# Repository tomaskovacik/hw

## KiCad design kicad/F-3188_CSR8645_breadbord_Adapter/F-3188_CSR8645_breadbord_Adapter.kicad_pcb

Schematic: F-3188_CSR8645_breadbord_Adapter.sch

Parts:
C1, C2: 100n; C_0805_HandSoldering
C3: 15p; C_0805_HandSoldering
D1, D2, D6: LED1; LED_1206_HandSoldering
D3, D4, D5: CG0603MLC-05E; R_0603_HandSoldering
D7: 1N4448; D_SOD-323_HandSoldering
J1: SCJ368R1NUS0B00G; 3.5mm_stereo_jack_PJ306M
J2: USB_B_Micro; USB_Micro-B
JP1: Jumper; SolderJumper-2_P1.3mm_Open_RoundedPad1.0x1.5mm
L1: 15nH; Choke_SMD_1206_Handsoldering
P1: CONN_01X22; Pin_Header_Straight_1x22
P2: CONN_01X21; Pin_Header_Straight_1x21
R1, R2, R5, R6: 10k; R_0805_HandSoldering
R3, R4, R9: 1k; R_0805_HandSoldering
R7, R8: 22; R_0805_HandSoldering
SW1: RESET; SW_SPST_FSMSM
SW2: VOL+; SW_SPST_FSMSM
SW3: VOL-; SW_SPST_FSMSM
SW4: NEXt; SW_SPST_FSMSM
SW5: PREV; SW_SPST_FSMSM
SW6: PLAY; SW_SPST_FSMSM
U1: F-3188_CSR8645; F-3188_CSR8645_no_silk_under_antena
U2: MIC; 3.5mm_stereo_jack_PJ320B

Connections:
5V: D5.1 (A1), D7.2 (A), J2.1 (VBUS)
/BAT: D7.1 (K), P1.14, R1.1, R2.1, R3.1, R4.1, R6.2, R9.1, U1.14 (BAT)
/HGND: J1.1, P2.3, U1.41 (SPK_L_N1)
/HL: J1.2, P2.4, U1.40 (SPK_R_P1)
/HR: J1.5, P2.2, U1.42 (SPK_L_P1)
/LED0: D2.1 (K), P1.3, U1.3 (LED0)
/LED1: D1.1 (K), P1.2, U1.2 (LED1)
/LED2: D6.1 (K), P1.1, U1.1 (LED2)
/MIC_AN: C1.1, P2.9, U1.35 (MIC_AN)
/MIC_AP: C2.2, P2.8, U1.36 (MIC_AP)
/MIC_BIAS: C1.2, P2.10, R5.1, U1.34 (MIC_BIAS)
/MIC_BN: P2.7, U1.37 (MIC_BN)
/MIC_BP: P2.6, U1.38 (MIC_BP)
/MUTE: P2.18, U1.26 (MUTE)
/NEXT: P2.13, SW4.2, U1.31 (NEXT)
/PLAY: P2.16, SW6.2, U1.28 (PLAY)
/POWER_ON: JP1.1, JP1.2, P1.15, R2.2, U1.15 (POWER_ON)
/PREV: P2.14, SW5.2, U1.30 (PREV)
/RST#: P1.13, R1.2, SW1.1, U1.13 (RST#)
/USB+: P2.19, R7.1, U1.25 (USB_P)
/USB-: P2.20, R8.1, U1.24 (USB_N)
/VOLDOWN: P2.12, SW3.2, U1.32 (VOLDOWN)
/VOLUP: P2.11, SW2.2, U1.33 (VOLUP)
GND: C3.2, D3.2 (A2), D4.2 (A2), D5.2 (A2), J2.5 (GND), J2.6 (Shield), P1.17, SW1.2, U1.17 (GND), U2.1
unnamed: C2.1, C3.1, L1.1, R5.2
unnamed: D1.2 (A), R9.2
unnamed: D2.2 (A), R4.2
unnamed: D3.1 (A1), J2.3 (D+), R7.2
unnamed: D4.1 (A1), J2.2 (D-), R8.2
unnamed: D6.2 (A), R3.2
unnamed: L1.2, U2.2
unnamed: P1.4, U1.4 (AIO0)
unnamed: P1.5, U1.5 (MISO)
unnamed: P1.6, U1.6 (CSB)
unnamed: P1.7, U1.7 (SPI_CLK)
unnamed: P1.8, U1.8 (MOSI)
unnamed: P1.9, U1.9 (SPI_PCM)
unnamed: P1.10, U1.10 (TX)
unnamed: P1.11, U1.11 (RX)
unnamed: P1.12, U1.12 (VBUS)
unnamed: P1.16, U1.16 (1V8)
unnamed: P1.18, U1.18 (CHG_EXT)
unnamed: P1.19, U1.19 (BAT_SENSE)
unnamed: P1.20, U1.20 (PIO10)
unnamed: P1.21, U1.21 (PIO11)
unnamed: P1.22, U1.22 (PIO12)
unnamed: P2.1, U1.43 (AGND)
unnamed: P2.5, U1.39 (SPK_R_N1)
unnamed: P2.15, U1.29 (GPIO8)
unnamed: P2.17, U1.27 (GPIO6)
unnamed: P2.21, U1.23 (PIO13)
unnamed: R6.1, SW2.1, SW3.1, SW4.1, SW5.1, SW6.1

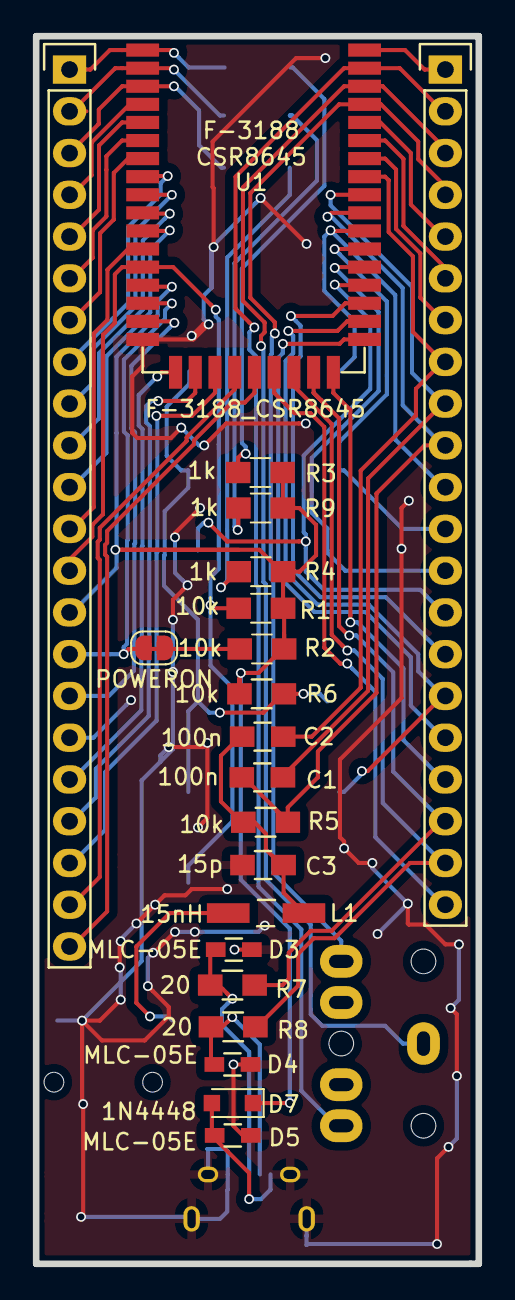
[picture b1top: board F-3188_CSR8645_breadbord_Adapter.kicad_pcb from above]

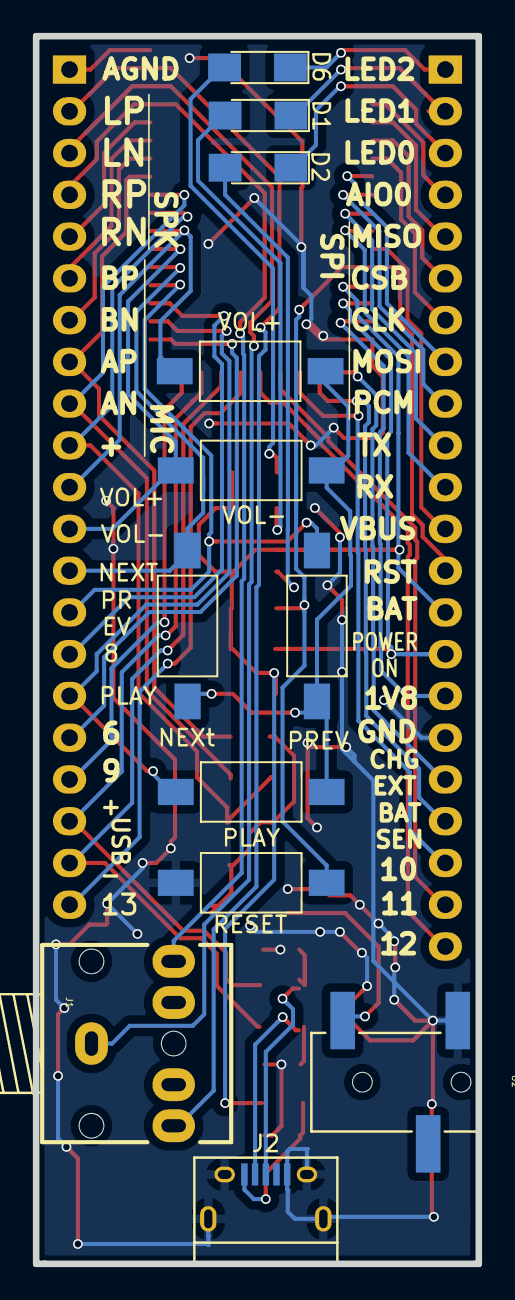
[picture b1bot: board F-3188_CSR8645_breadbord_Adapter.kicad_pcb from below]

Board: 2 copper layers, 26.9 x 74.7 mm, 33 parts (12 on the bottom side), 52 nets.

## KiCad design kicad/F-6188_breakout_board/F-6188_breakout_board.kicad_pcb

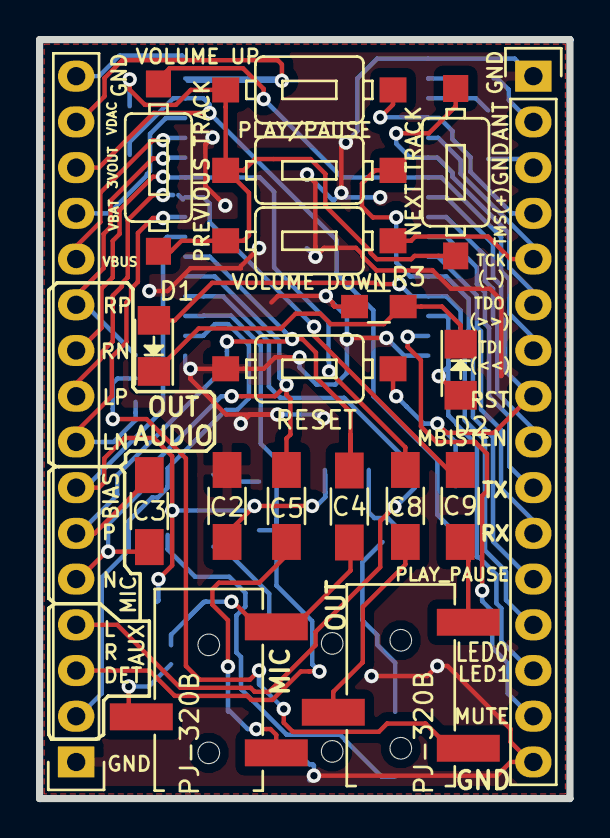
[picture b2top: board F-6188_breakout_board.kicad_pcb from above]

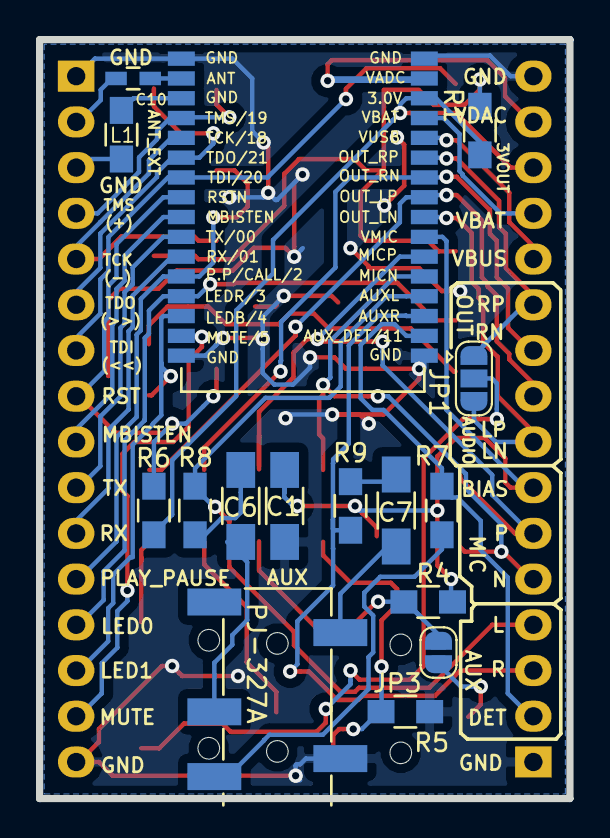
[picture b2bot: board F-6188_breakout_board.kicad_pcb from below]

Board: 2 copper layers, 29.5 x 42.2 mm, 35 parts (16 on the bottom side), 44 nets.

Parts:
C1: 100n/50V X7R!!!; C_1206_HandSoldering
C2: 1u/16V; C_1206_HandSoldering
C3: 10n/50V X7R!!!; C_1206_HandSoldering
C4, C5: 1u/16V X7R; C_1206_HandSoldering
C6, C7: 1u/25V; C_1206_HandSoldering
C8, C9: CKS1206 10u/25V X5R 10% SAMSUNG; C_1206_HandSoldering
C10: 2.2p; C_0603_HandSoldering
CON1, CON2: CONN_16; Pin_Header_Straight_1x16
D1, D2: LED; LED-1206
JP1: Jumper_3_Bridged12; SolderJumper-3_P1.3mm_Open_RoundedPad1.0x1.5mm
JP3: Jumper_NO_Small; SolderJumper-2_P1.3mm_Open_RoundedPad1.0x1.5mm
L1: 100nH*; R_0805_HandSoldering
R1, R6: 10k; R_0805_HandSoldering
R3, R4, R5, R7, R8, R9: 1k; R_0805_HandSoldering
SW1: VOLUME UP; 3x6x2.5mm_tact_switch
SW2: VOLUME DOWN; 3x6x2.5mm_tact_switch
SW3: NEXT TRACK; 3x6x2.5mm_tact_switch
SW4: PREVIOUS TRACK; 3x6x2.5mm_tact_switch
SW5: PLAY/PAUSE; 3x6x2.5mm_tact_switch
SW6: RESET; 3x6x2.5mm_tact_switch
U1: F-6188
U2, U3: PJ-320B; 3.5mm_stereo_jack_PJ320B
U4: PJ-327A

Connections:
/3V_OUT: CON1.14, R1.1, R6.1, U1.30
/#RST: CON2.8, R6.2, SW6.2, U1.8
/ANT_EXT: C10.1, U1.2
/AUDIO_LN: CON1.8, JP1.3, U1.24
/AUDIO_LP: C9.1, CON1.9, U1.25
/AUDIO_RN: CON1.11, JP1.1, U1.27
/AUDIO_RP: C8.1, CON1.10, U1.26
/AUX_DETECT: CON1.2, R7.1, U1.18
/AUX_INL: CON1.4, R8.1, U1.20
/AUX_INR: CON1.3, R9.1, U1.19
/LED0: CON2.13, D1.2, U1.13
/LED1: CON2.14, D2.2, U1.14
/MBISTEN: CON2.9, U1.9
/MICN: C3.1, C5.1, CON1.5, U1.21
/MICP: C3.2, C4.1, CON1.6, U1.22
/MIC_BIAS: C1.2, C2.1, CON1.7, R4.2, U1.23
/MUTE: CON2.15, U1.15
/PLAY_PAUSE: CON2.12, SW5.2, U1.12
/RX: CON2.11, U1.11
/TCK: CON2.5, SW2.2, U1.5
/TDI: CON2.7, SW4.2, U1.7
/TDO: CON2.6, SW3.2, U1.6
/TMS: CON2.4, SW1.2, U1.4
/TX: CON2.10, U1.10
/VBAT: CON1.13, U1.29
/VBUS: CON1.12, U1.28
/VDAC: CON1.15, U1.31
GND: C1.1, C2.2, CON1.1, CON1.16, CON2.1, CON2.16, R3.2, R5.1, SW6.1, U1.1, U1.16, U1.17, U1.32, U4.3
unnamed: C4.2, JP3.1, R4.1, U2.2
unnamed: C5.2, R5.2, U2.1
unnamed: C6.1, R8.2
unnamed: C6.2, U4.5
unnamed: C7.1, R9.2
unnamed: C7.2, U4.2
unnamed: C8.2, U3.3
unnamed: C9.2, U3.2
unnamed: C10.2, CON2.2
unnamed: CON2.3, L1.2
unnamed: D1.1, D2.1, R3.1
unnamed: JP1.2, U3.1
unnamed: JP3.2, U2.3
unnamed: L1.1, U1.3
unnamed: R1.2, SW1.1, SW2.1, SW3.1, SW4.1, SW5.1
unnamed: R7.2, U4.4

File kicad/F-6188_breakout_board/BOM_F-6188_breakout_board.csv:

"Id";"Designator";"Package";"Quantity";"Designation";"Supplier and ref";
1;"SW6";"3x6x2.5mm_tact_switch";1;"RESET";;;
2;"SW3";"3x6x2.5mm_tact_switch";1;"NEXT TRACK";;;
3;"SW4";"3x6x2.5mm_tact_switch";1;"PREVIOUS TRACK";;;
4;"SW2";"3x6x2.5mm_tact_switch";1;"VOLUME DOWN";;;
5;"SW5";"3x6x2.5mm_tact_switch";1;"PLAY/PAUSE";;;
6;"SW1";"3x6x2.5mm_tact_switch";1;"VOLUME UP";;;
7;"U2,U3";"3.5mm_stereo_jack_PJ320B";2;"PJ-320B";;;
8;"C2";"TantalC_SizeA_EIA-3216_HandSoldering";1;"CTS 1u/16V A 10% AVX-TAJ";;;
9;"CON1,CON2";"Pin_Header_Straight_1x16";2;"CONN_16";;;
10;"D1,D2";"LED-1206";2;"LED";;;
11;"R1,R6";"R_0805_HandSoldering";2;"10k";;;
12;"R2,R3,R7,R8,R9";"R_0805_HandSoldering";5;"1k";;;
13;"R4,R5";"R_0805_HandSoldering";2;"1k2";;;
14;"U1";"F-6188";1;"F-6188";;;
15;"U4";"PJ-327A";1;"PJ-327A";;;
16;"C1,C3";"C_1206_HandSoldering";2;"100n/50V X7R!!!";;;
17;"C6,C7,C8,C9";"C_1206_HandSoldering";4;"CKS1206 10u/25V X5R 10% SAMSUNG";;;
18;"JP2";"SolderJumper-2_P1.3mm_Open_RoundedPad1.0x1.5mm";1;"Jumper_2";;;
19;"JP1";"SolderJumper-3_P1.3mm_Open_RoundedPad1.0x1.5mm";1;"Jumper_3_Bridged12";;;
20;"JP3";"SolderJumper-2_P1.3mm_Open_RoundedPad1.0x1.5mm";1;"Jumper_NO_Small";;;
21;"C4,C5";"C_1206_HandSoldering";2;"1u/16V X7R";;;

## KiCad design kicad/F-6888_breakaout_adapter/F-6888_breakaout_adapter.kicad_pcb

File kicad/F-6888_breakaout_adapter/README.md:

# IMPORTANT NOTE

take care what module you buy, where are version which did not have support for all features,read description of what you buy, for example here from aliexpress:

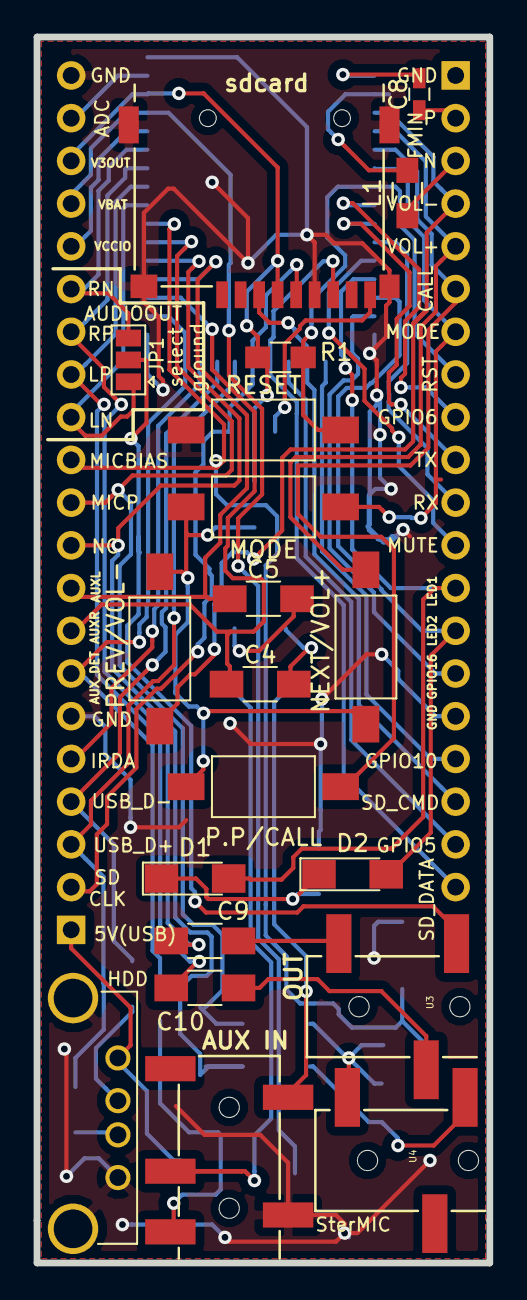
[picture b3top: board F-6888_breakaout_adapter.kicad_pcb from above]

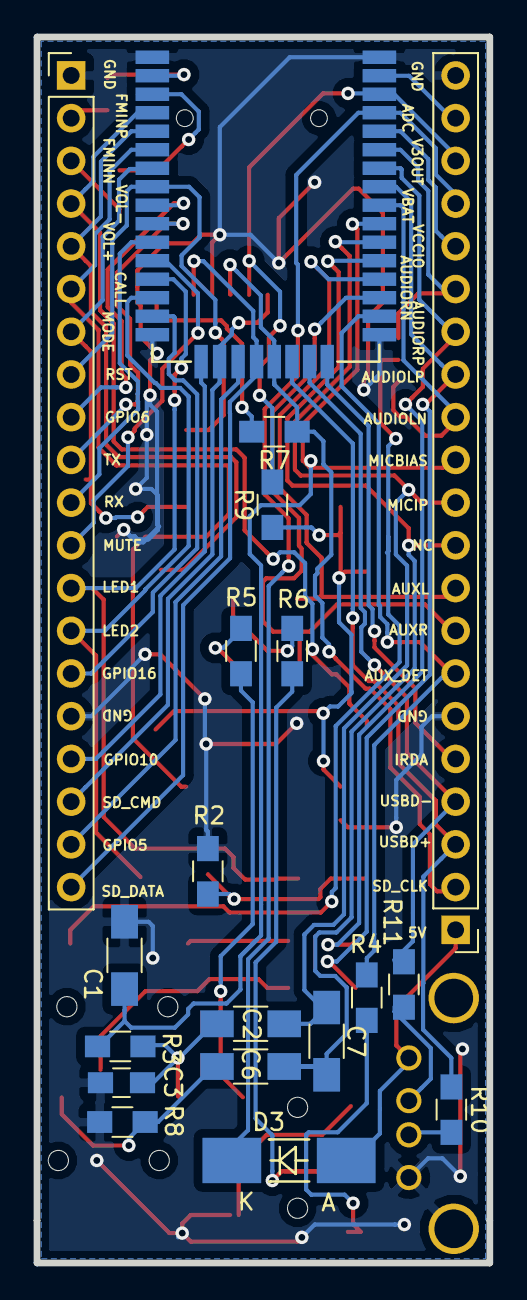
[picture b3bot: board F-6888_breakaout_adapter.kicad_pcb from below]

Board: 2 copper layers, 26.9 x 72.9 mm, 39 parts (19 on the bottom side), 55 nets.

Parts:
C1, C2, C4, C5, C9, C10: 1uF; C_1206_HandSoldering
C3: 100p; C_0805_HandSoldering
C6: 1uF*; C_1206_HandSoldering
C7: 10n(*); C_1206_HandSoldering
C8: 2.2p; C_0603_HandSoldering
D1, D2: LED; LED_1206_HandSoldering
D3: D; MELF_Handsoldering
J1: USB_A
J2: CONN_01X20; Pin_Header_Straight_1x20_Pitch2.54mm
J4: CONN_01X20; Pin_Header_Straight_1x21_Pitch2.54mm
J6: Micro_SD_Card_Det; Conn_uSDcard
JP1: Jumper_NC_Dual; SolderJumper-3_P1.3mm_Open_Pad1.0x1.5mm
L1: 100nH*; R_0805_HandSoldering
R1, R9: 10k; R_0805_HandSoldering
R2, R3, R4, R5, R6: 1k; R_0805_HandSoldering
R7: 3k3; R_0805_HandSoldering
R8: 1k*; R_0805_HandSoldering
R10, R11: 200; R_0805_HandSoldering
SW1: RESET; SW_SPST_FSMSM
SW2: PREV/VOL-; SW_SPST_FSMSM
SW3: NEXT/VOL+; SW_SPST_FSMSM
SW4: P.P/CALL; SW_SPST_FSMSM
SW5: MODE; SW_SPST_FSMSM
U1: F-6888
U2: PJ-327A
U3, U4: PJ-320B; 3.5mm_stereo_jack_PJ320B

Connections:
/5V: D3.2, J1.1, J4.1
/ADC: J4.20, U1.39
/AUDIOLN: J4.13, JP1.1, U1.32
/AUDIOLP: C10.2, J4.14, U1.33
/AUDIORN: J4.16, JP1.3, U1.35
/AUDIORP: C9.2, J4.15, U1.34
/AUXL: C5.1, J4.9, U1.28
/AUXR: C4.1, J4.8, U1.27
/AUX_DET: J4.7, R4.1, U1.26
/FMINN: L1.2, U1.3
/FMINP: C8.2, U1.2
/GPIO5: J2.19, U1.19
/GPIO6: J2.9, U1.9
/GPIO10: J2.17, U1.17
/GPIO16: J2.15, U1.15
/IRDA: J4.5, U1.24
/LED1: D1.2, J2.13, U1.13
/LED2: D2.2, J2.14, U1.14
/MICBIAS: C1.1, J4.12, R3.2, U1.31
/MICIP: C2.2, C7.1, J4.11, U1.30
/MODE: J2.7, SW5.2, U1.7
/MUTE: J2.12, U1.12
/NC: C6.1, C7.2, J4.10, U1.29
/NEXT/VOL+: J2.5, SW3.2, U1.5
/P.P/CALL: J2.6, SW4.2, U1.6
/PREV/VOL-: J2.4, SW2.2, U1.4
/RSTN: J2.8, R1.1, SW1.2, U1.8
/RX: J2.11, U1.11
/SD_CLK: J4.2, J6.5, R7.1, U1.21
/SD_CMD: J2.18, J6.3, U1.18
/SD_DATA: J2.20, J6.7, U1.20
/TX: J2.10, U1.10
/USBD+: J4.3, R10.1, U1.22
/USBD-: J4.4, R11.2, U1.23
/V3OUT: J4.19, J6.4, R1.2, R9.2, U1.38
/VBAT: D3.1, J4.18, U1.37
/VCCIO: J4.17, U1.36
GND: C1.2, C3.2, J1.4, J1.5, J2.1, J2.16, J4.6, J4.21, J6.6, R2.2, R8.1, SW1.1, U1.1, U1.16, U1.25, U1.40, U2.3
unnamed: C2.1, C3.1, R3.1, U4.2
unnamed: C4.2, R5.1
unnamed: C5.2, R6.1
unnamed: C6.2, R8.2, U4.1
unnamed: C8.1, J2.2
unnamed: C9.1, U3.2
unnamed: C10.1, U3.3
unnamed: D1.1, D2.1, R2.1
unnamed: J1.2, R11.1
unnamed: J1.3, R10.2
unnamed: J2.3, L1.1
unnamed: J6.9, R7.2
unnamed: JP1.2, U3.1
unnamed: R4.2, U2.4
unnamed: R5.2, U2.2
unnamed: R6.2, U2.5
unnamed: R9.1, SW2.1, SW3.1, SW4.1, SW5.1

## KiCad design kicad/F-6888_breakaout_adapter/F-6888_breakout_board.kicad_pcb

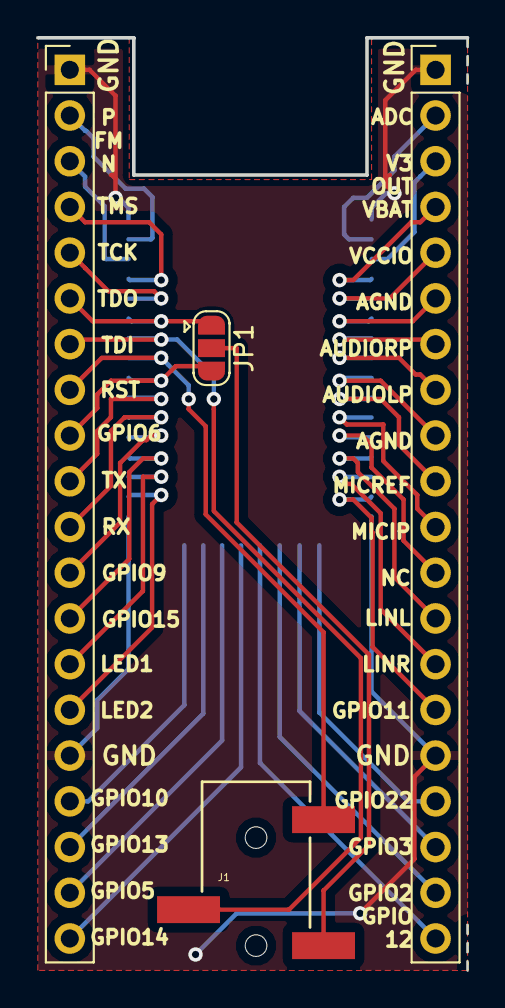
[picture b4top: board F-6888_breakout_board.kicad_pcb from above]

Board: 2 copper layers, 23.9 x 51.8 mm, 5 parts (1 on the bottom side), 38 nets.

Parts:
CON1, CON2: CONN_20; Pin_Header_Straight_1x20_Pitch2.54mm
J1: Jack_3.5mm_5pin; 3.5mm_stereo_jack_PJ320B_no_up_silkscreen
JP1: JUMPER3; SolderJumper-3_P1.3mm_Open_RoundedPad1.0x1.5mm
U1: F-6888

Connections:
GND: CON1.1, CON1.16, CON2.1, CON2.16, U1.1, U1.16, U1.25, U1.40
unnamed: CON1.2, U1.2
unnamed: CON1.3, U1.3
unnamed: CON1.4, U1.4
unnamed: CON1.5, U1.5
unnamed: CON1.6, U1.6
unnamed: CON1.7, U1.7
unnamed: CON1.8, U1.8
unnamed: CON1.9, U1.9
unnamed: CON1.10, U1.10
unnamed: CON1.11, U1.11
unnamed: CON1.12, U1.12
unnamed: CON1.13, U1.13
unnamed: CON1.14, U1.14
unnamed: CON1.15, U1.15
unnamed: CON1.17, U1.17
unnamed: CON1.18, U1.18
unnamed: CON1.19, U1.19
unnamed: CON1.20, U1.20
unnamed: CON2.2, U1.39
unnamed: CON2.3, U1.38
unnamed: CON2.4, U1.37
unnamed: CON2.5, U1.36
unnamed: CON2.6, JP1.1, U1.35
unnamed: CON2.7, J1.2, U1.34
unnamed: CON2.8, J1.5, U1.33
unnamed: CON2.9, JP1.3, U1.32
unnamed: CON2.10, U1.31
unnamed: CON2.11, U1.30
unnamed: CON2.12, U1.29
unnamed: CON2.13, U1.28
unnamed: CON2.14, U1.27
unnamed: CON2.15, U1.26
unnamed: CON2.17, U1.24
unnamed: CON2.18, U1.23
unnamed: CON2.19, U1.22
unnamed: CON2.20, U1.21
unnamed: J1.1, JP1.2

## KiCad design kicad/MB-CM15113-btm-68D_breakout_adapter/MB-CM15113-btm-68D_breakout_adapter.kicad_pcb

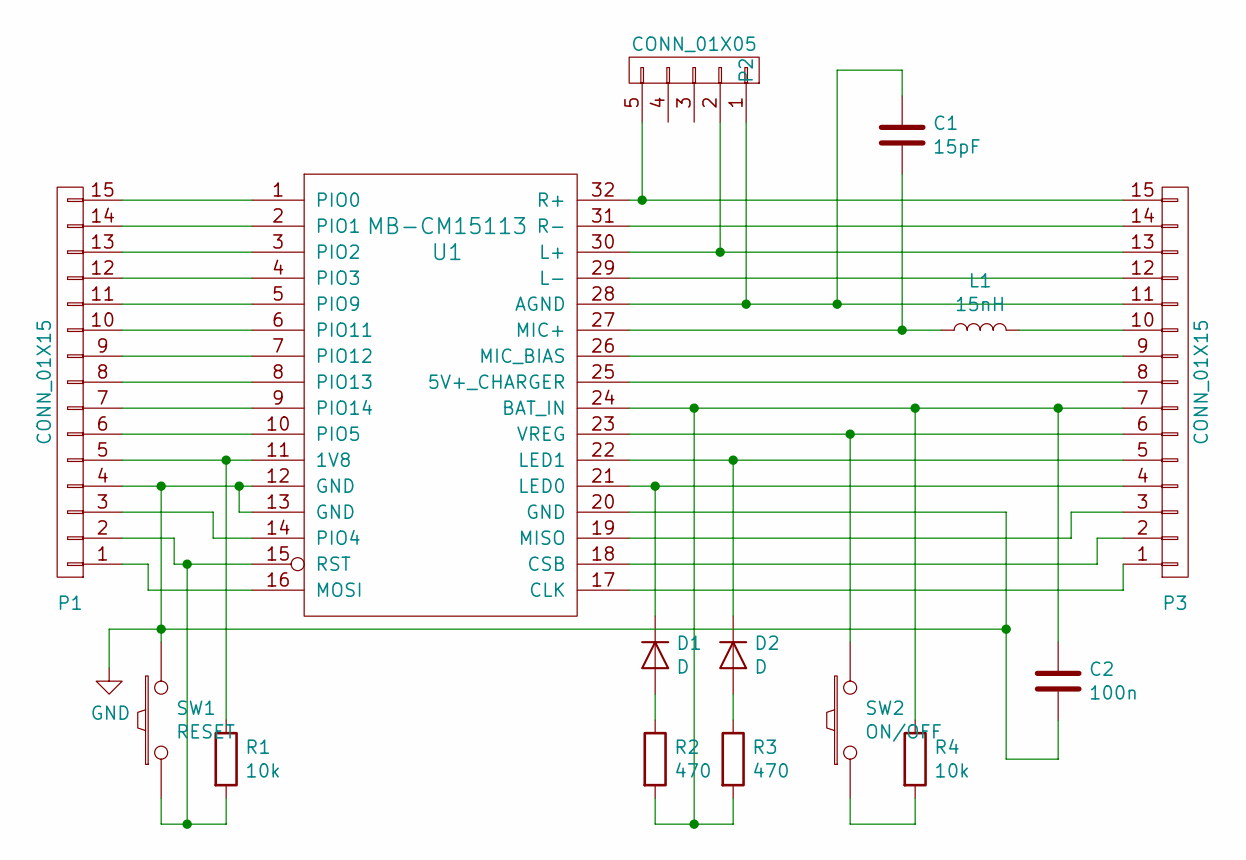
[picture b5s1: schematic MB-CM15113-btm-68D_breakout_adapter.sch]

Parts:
C1: 15pF; C_0805_HandSoldering
C2: 100n; C_0805_HandSoldering
D1, D2: D; LED-1206
L1: 15nH; Choke_SMD_1206_Standard
P1, P3: CONN_01X15; Pin_Header_Straight_1x15_Pitch2.54mm
P2: CONN_01X05; 3.5mm_stereo_jack_PJ320B
R1, R4: 10k; R_0805_HandSoldering
R2, R3: 470; R_0805_HandSoldering
SW1: RESET; SW_SPST_FSMSM
SW2: ON/OFF; SW_SPST_FSMSM
U1: MB-CM15113

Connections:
GND: C2.2, P1.4, SW1.2, U1.12 (GND), U1.13 (GND), U1.20 (GND)
unnamed: C1.1, P2.1, P3.11, U1.28 (AGND)
unnamed: C1.2, L1.1, U1.27 (MIC+)
unnamed: C2.1, P3.7, R2.2, R3.2, R4.1, U1.24 (BAT_IN)
unnamed: D1.1 (K), P3.4, U1.21 (LED0)
unnamed: D1.2 (A), R2.1
unnamed: D2.1 (K), P3.5, U1.22 (LED1)
unnamed: D2.2 (A), R3.1
unnamed: L1.2, P3.10
unnamed: P1.1, U1.16 (MOSI)
unnamed: P1.2, R1.2, SW1.1, U1.15 (RST)
unnamed: P1.3, U1.14 (PIO4)
unnamed: P1.5, R1.1, U1.11 (1V8)
unnamed: P1.6, U1.10 (PIO5)
unnamed: P1.7, U1.9 (PIO14)
unnamed: P1.8, U1.8 (PIO13)
unnamed: P1.9, U1.7 (PIO12)
unnamed: P1.10, U1.6 (PIO11)
unnamed: P1.11, U1.5 (PIO9)
unnamed: P1.12, U1.4 (PIO3)
unnamed: P1.13, U1.3 (PIO2)
unnamed: P1.14, U1.2 (PIO1)
unnamed: P1.15, U1.1 (PIO0)
unnamed: P2.2, P3.13, U1.30 (L+)
unnamed: P2.5, P3.15, U1.32 (R+)
unnamed: P3.1, U1.17 (CLK)
unnamed: P3.2, U1.18 (CSB)
unnamed: P3.3, U1.19 (MISO)
unnamed: P3.6, SW2.2, U1.23 (VREG)
unnamed: P3.8, U1.25 (5V+_CHARGER)
unnamed: P3.9, U1.26 (MIC_BIAS)
unnamed: P3.12, U1.29 (L-)
unnamed: P3.14, U1.31 (R-)
unnamed: R4.2, SW2.1

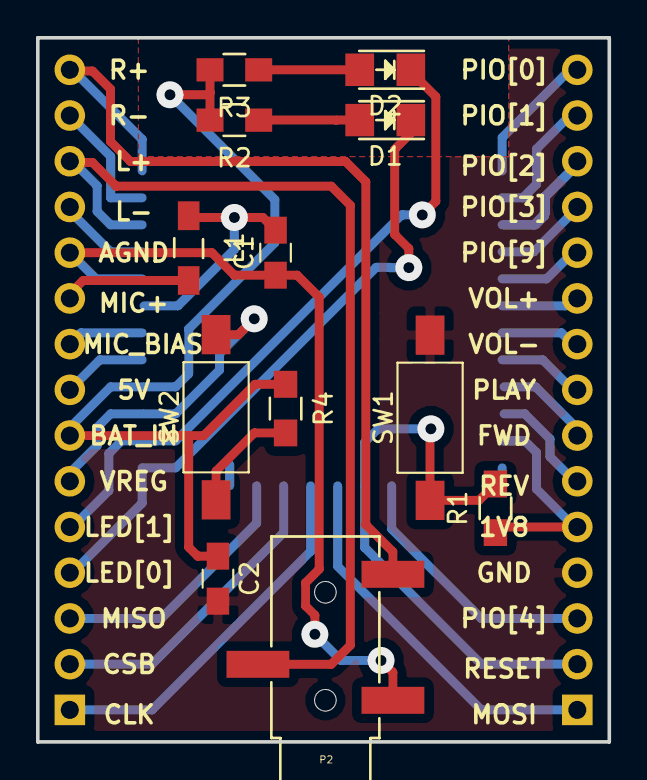
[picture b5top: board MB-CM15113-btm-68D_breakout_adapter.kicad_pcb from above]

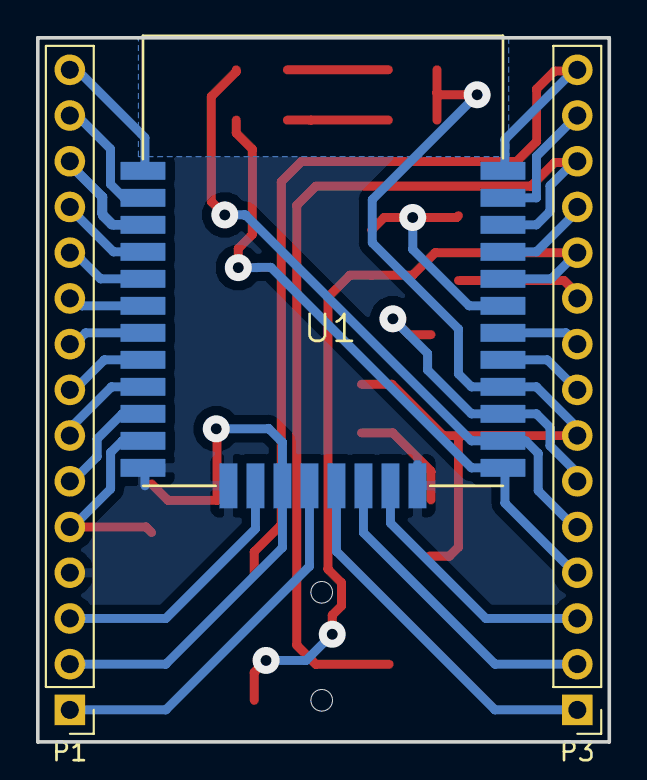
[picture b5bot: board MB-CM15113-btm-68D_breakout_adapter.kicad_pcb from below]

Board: 2 copper layers, 31.8 x 39.1 mm, 15 parts (3 on the bottom side), 34 nets.
